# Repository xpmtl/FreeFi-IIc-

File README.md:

# FreeFi-IIc-
FreeFi for the Apple IIc+

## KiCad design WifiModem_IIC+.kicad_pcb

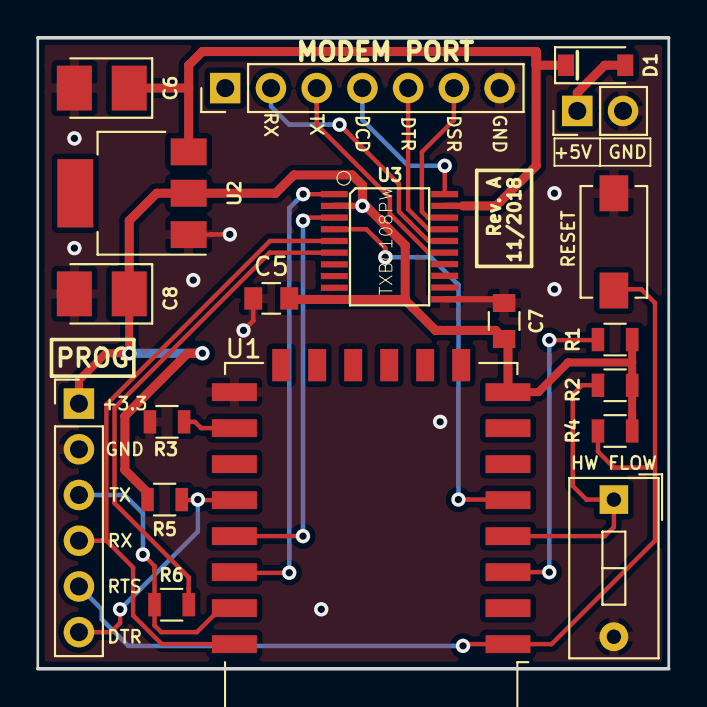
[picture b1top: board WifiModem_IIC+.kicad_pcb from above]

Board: 2 copper layers, 35.1 x 35.1 mm, 19 parts (0 on the bottom side), 20 nets.

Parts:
C5, C7: 100nF; C_0805
C6, C8: 10uF; CP_Tantalum_Case-B_EIA-3528-21_Reflow
D1: 1N5819; D_SOD-123
J2: Serial Prog.; Pin_Header_Straight_1x06_Pitch2.54mm
J3: To IIc+; Pin_Header_Straight_1x07_Pitch2.54mm
J5: POWER; Pin_Header_Straight_1x02_Pitch2.54mm
R1, R2, R3, R4, R5: 10K; R_0805
R6: 470R; R_0805
SW2: SW_DIP_x01; SW_DIP_x1_W7.62mm_Slide
SW3: SW_Push; SW_SPST_EVQPE1
U1: ESP-12E
U2: LM1117-3.3; SOT-223
U3: TXB0108PW; TSSOP20-0.65-6.5X4.4MM

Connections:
+3V3: C5.1, C7.1, C8.1, J2.1, R1.1, R2.1, R4.2, R5.2, U1.8, U2.2, U3.2, U3.10
+5V: C6.1, D1.1, U2.3, U3.19
DCD: J3.4, U3.20
DSR: J3.6, U3.18
DTR: J3.5, U3.17
GND: C5.2, C6.2, C7.2, C8.2, J2.2, J3.7, J5.2, R3.1, SW2.2, SW3.2, U1.15, U2.1, U3.11
GPIO4: U1.19, U3.3
GPIO5: U1.20, U3.1
GPIO14: U1.5, U3.4
GPIO15: R3.2, U1.16
GPIO16: R2.2, SW2.1, U1.4
unnamed: D1.2, J5.1
unnamed: R1.2, U1.3
RESET: J2.5, R4.1, SW3.1, U1.1
RXD0: J2.3, R6.1, U1.21
RXD0A: R6.2, U3.6
Rx: J3.2, U3.16
TXD0: J2.4, U1.22, U3.5
Tx: J3.3, U3.15
iDTR: J2.6, R5.1, U1.18

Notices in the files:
WifiModem_IIC+.kicad_pcb:
(c) 2018 Daniel Jameson
(c) 2018 Terence Hacke®
